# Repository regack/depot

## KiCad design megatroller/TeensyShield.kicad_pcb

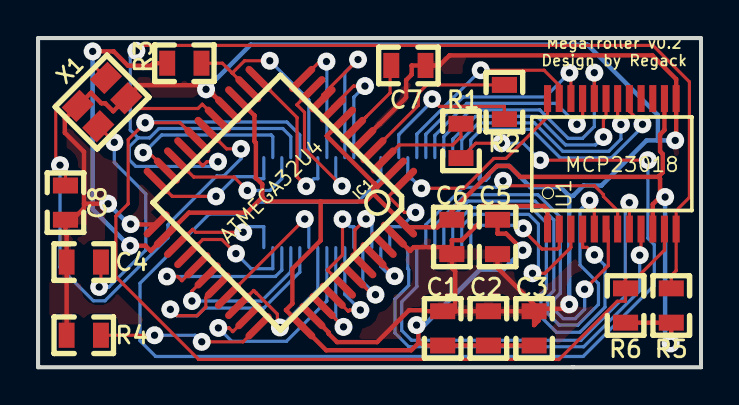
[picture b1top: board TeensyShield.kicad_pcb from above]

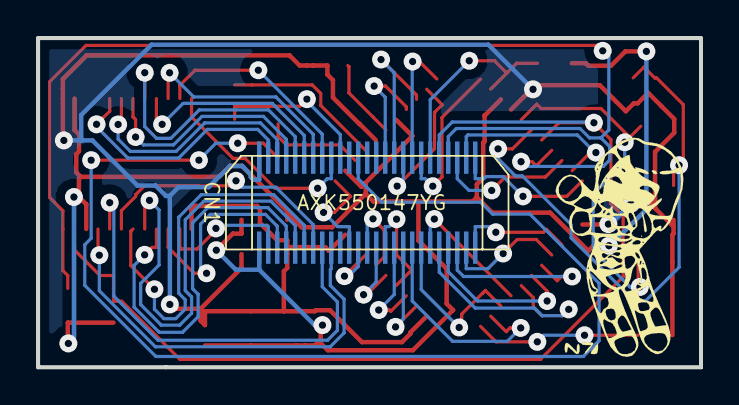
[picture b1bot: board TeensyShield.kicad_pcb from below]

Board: 2 copper layers, 36.8 x 18.3 mm, 19 parts (2 on the bottom side), 52 nets.

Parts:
C1, C7: 1u; SM0805
C2, C3, C5, C6: 100n; SM0805
C4, C8: 22p; SM0805
CN1: AXK550147YG; Panasonic_AXK550147YG_Socket
G1: LOGO; Silkscreen_Regack_100x150rev
IC1: ATMEGA32U4; TQFP44
R1, R2: 22Ω; SM0805
R3, R4: 10kΩ; SM0805
R5, R6: 2.2kΩ; SM0805
U1: MCP23018; SSOP24
X1: 7M-16.000MAAJ-T; ASX3F

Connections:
/GPA0: CN1.3, U1.17
/GPA1: CN1.5, U1.18
/GPA2: CN1.7, U1.19
/GPA3: CN1.9, U1.20
/GPA4: CN1.11, U1.21
/GPA5: CN1.13, U1.22
/GPA6: CN1.15, U1.23
/GPA7: CN1.17, U1.24
/GPB0: CN1.4, U1.2
/GPB1: CN1.6, U1.3
/GPB2: CN1.8, U1.4
/GPB3: CN1.10, U1.5
/GPB4: CN1.12, U1.6
/GPB5: CN1.14, U1.7
/GPB6: CN1.16, U1.8
/GPB7: CN1.18, U1.9
/PB0: CN1.29, IC1.8
/PB1: CN1.31, IC1.9
/PB2: CN1.33, IC1.10
/PB3: CN1.35, IC1.11
/PB4: CN1.44, IC1.28
/PB5: CN1.42, IC1.29
/PB6: CN1.40, IC1.30
/PB7: CN1.37, IC1.12
/PC6: CN1.38, IC1.31
/PC7: CN1.36, IC1.32
/PD0: CN1.41, IC1.18, R6.2, U1.11
/PD1: CN1.43, IC1.19, R5.2, U1.12
/PD2: CN1.45, IC1.20
/PD3: CN1.47, IC1.21
/PD4: CN1.50, IC1.25
/PD5: CN1.49, IC1.22
/PD6: CN1.48, IC1.26
/PD7: CN1.46, IC1.27
/PE6: CN1.22, IC1.1
/PF0: CN1.24, IC1.41
/PF1: CN1.26, IC1.40
/PF4: CN1.28, IC1.39
/PF5: CN1.30, IC1.38
/PF6: CN1.32, IC1.37
/PF7: CN1.34, IC1.36
/RST: CN1.39, IC1.13, R3.2
/USB_D+: CN1.19, R2.1
/USB_D-: CN1.23, R1.1
GND: C1.2, C2.2, C3.2, C4.2, C5.2, C6.2, C7.2, C8.2, CN1.1, IC1.5, IC1.15, IC1.23, IC1.35, IC1.43, R4.2, U1.1, U1.13, X1.2, X1.4
unnamed: C4.1, IC1.16, X1.1
unnamed: C7.1, IC1.6
unnamed: IC1.4, R2.2
unnamed: IC1.3, R1.2
unnamed: IC1.33, R4.1
unnamed: C8.1, IC1.17, X1.3
VCC: C1.1, C2.1, C3.1, C5.1, C6.1, CN1.2, IC1.2, IC1.7, IC1.14, IC1.24, IC1.34, IC1.44, R3.1, R5.1, R6.1, U1.10, U1.14

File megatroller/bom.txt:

ref             value           Item count      Mfr #                   footprint       datasheet
==========================================================================================================
C1, C7          1uF             1               VJ0805Y105JXQTW1BC      0805            https://www.mouser.com/Search/ProductDetail.aspx?R=VJ0805Y10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
C2,C3, C5, C6   0.1uF           2               VJ0805Y104JXXAC 0805                    https://www.mouser.com/Search/ProductDetail.aspx?R=VJ0805Y10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 
C4, C8          22pF            2               VJ0805A220GXXCW1BC      0805            https://www.mouser.com/Search/ProductDetail.aspx?R=VJ0805A22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 
CN1             AXK550147YG     1               AXK550147YG                             https://www.mouser.com/Search/ProductDetail.aspx?R=AXK550147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
IC1             ATMEGA32U4      1               ATMEGA32U4-AU-ND        TQFP44          https://www.mouser.com/Search/ProductDetail.aspx?R=ATMEGA32U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
R1,R2           22O             2               CRCW080522R0JNTABC      0805            http://www.tme.eu/pl/Document/e5152f6c2c4f933b61676f6de7ae79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
R3,R4           10kO            2               CRCW080510K0JNTABC      0805            http://www.tme.eu/pl/Document/e5152f6c2c4f933b61676f6de7ae79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
R5,R6           2.2kO           2               CRCW080522R0JNTABC      0805            http://www.tme.eu/pl/Document/e5152f6c2c4f933b61676f6de7ae79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
U1              MCP23018        1               MCP23018-E/SS           SSOP24          https://www.mouser.com/Search/ProductDetail.aspx?R=MCP23018-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
X1              7M-16.000MAAJ-T 1               7M-16.000MAAJ-T                         https://www.mouser.com/Search/ProductDetail.aspx?R=7M-16.000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

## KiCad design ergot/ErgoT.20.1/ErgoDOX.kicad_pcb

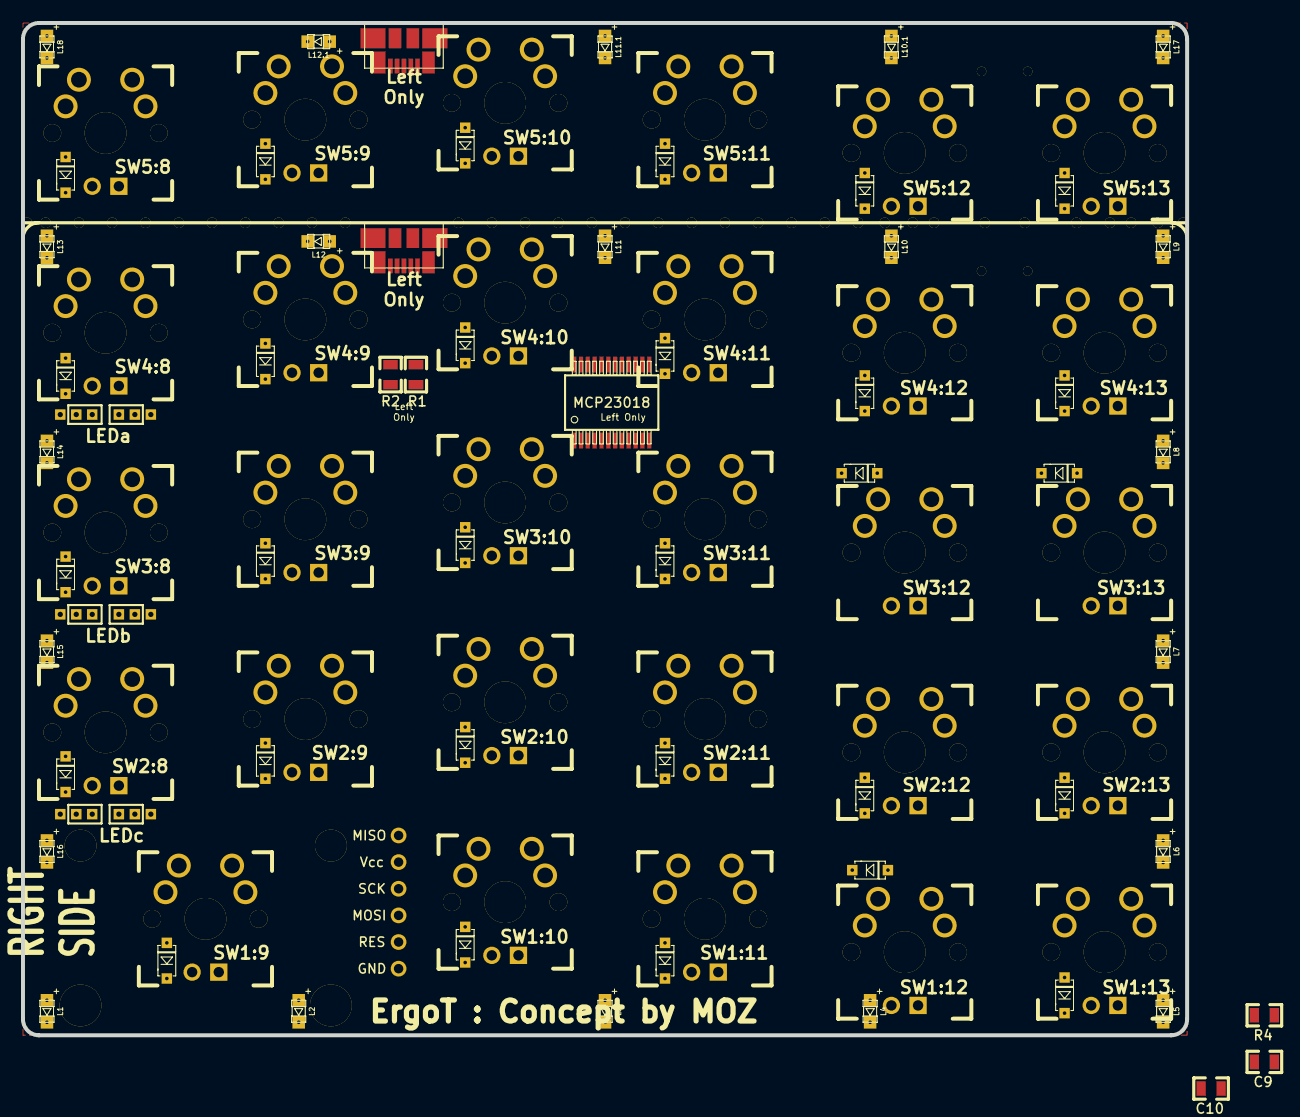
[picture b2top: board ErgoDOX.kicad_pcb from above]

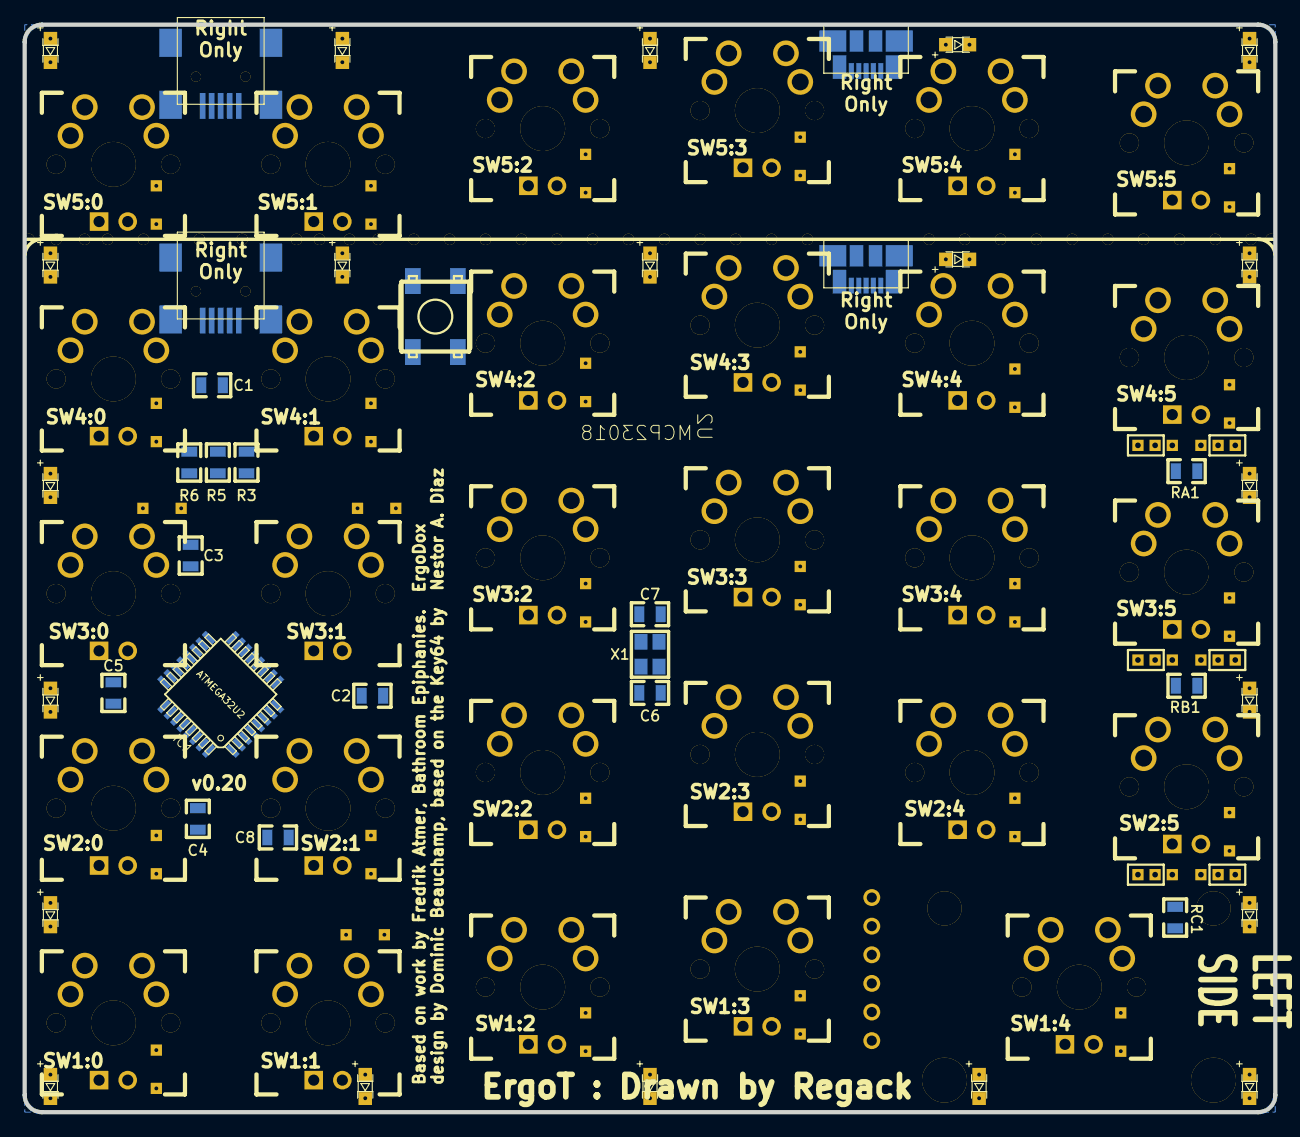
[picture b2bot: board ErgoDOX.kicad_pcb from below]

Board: 2 copper layers, 111.0 x 96.5 mm, 184 parts (21 on the bottom side), 81 nets, no tracks yet.

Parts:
C1, C8: 1u; SM0805
C2, C3, C4, C5: 100n; SM0805
C6, C7: 22p; SM0805
C9: 10μF; SM0805
C10: 0.1μF; SM0805
D1:9: D1:4; SOD-123_2Side
D1:10: D1:3; SOD-123_2Side
D1:11: D1:2; SOD-123_2Side
D1:12: D1:1; SOD-123_2Side
D1:13: D1:0; SOD-123_2Side
D2:8: D2:5; SOD-123_2Side
D2:9: D2:4; SOD-123_2Side
D2:10: D2:3; SOD-123_2Side
D2:11: D2:2; SOD-123_2Side
D2:12: D2:1; SOD-123_2Side
D2:13: D2:0; SOD-123_2Side
D3:8: D3:5; SOD-123_2Side
D3:9: D3:4; SOD-123_2Side
D3:10: D3:3; SOD-123_2Side
D3:11: D3:2; SOD-123_2Side
D3:12: D3:1; SOD-123_2Side
D3:13: D3:0; SOD-123_2Side
D4:8: D4:5; SOD-123_2Side
D4:9: D4:4; SOD-123_2Side
D4:10: D4:3; SOD-123_2Side
D4:11: D4:2; SOD-123_2Side
D4:12: D4:1; SOD-123_2Side
D4:13: D4:0; SOD-123_2Side
D5:8: D5:5; SOD-123_2Side
D5:9: D5:4; SOD-123_2Side
D5:10: D5:3; SOD-123_2Side
D5:11: D5:2; SOD-123_2Side
D5:12: D5:1; SOD-123_2Side
D5:13: D5:0; SOD-123_2Side
IC1: ATMEGA32U2; adafruit-TQFP32-08
J1, J1.1: USB; USB_MINI-B_OST_M26FTR
J2.1, J2.1.1: LEFT(TOP); USB_MICRO-B_MOLEX_47346-0001
J2.2, J2.2.1: RIGHT(BOTTOM); USB_MICRO-B_MOLEX_47346-0001
JP1, JP2, JP3, JP4, JP5, JP6: JUMPER3; 40milX3
L1, L2, L3, L4, L5, L6, L7, L8, L9, L10, L10.1, L11, L11.1, L12, L12.1, L13, L14, L15, L16, L17, L18: LED; LED0805_(1-2)_2Side
L1:0, L1:1, L1:2, L1:3, L1:4, L2:0, L2:1, L2:2, L2:3, L2:4, L2:5, L3:0, L3:1, L3:2, L3:3, L3:4, L3:5, L4:0, L4:1, L4:2, L4:3, L4:4, L4:5, L5:0, L5:1, L5:2, L5:3, L5:4, L5:5: LED; MX_LED
M1, M2, M3, M4, M5, M6, M7, M8, M9, M10, M11, M12, M13, M14, M15, M16, M17, M18, M19, M20, M21, M22, M23, M24, M25, M26, M27, M28, M29, M30, M31, M32, M33, M34: DRILL; Pad_Drl
P1: MISO; Pad
P4: Vcc; Pad
P5: SCK; Pad
P6: MOSI; Pad
P7: RES; Pad
P8: GND; Pad
R1, R2: 2.2kΩ; SM0805
R3: 10k; SM0805
R4: 22.6k; SM0805
R5, R6: 22; SM0805
RA1: LEDa; SM0805
RB1: LEDb; SM0805
RC1: LEDc; SM0805
S0: DTSM-6; ADTSJW65RV
S2: STAB200; STAB_PCB940
SW1:9: SW1:4; MX_FLIP
SW1:10: SW1:3; MX_FLIP
SW1:11: SW1:2; MX_FLIP
SW1:12: SW1:1; MX_FLIP
SW1:13: SW1:0; MX_FLIP
SW2:8: SW2:5; MX_FLIP
SW2:9: SW2:4; MX_FLIP
SW2:10: SW2:3; MX_FLIP
SW2:11: SW2:2; MX_FLIP
SW2:12: SW2:1; MX_FLIP
SW2:13: SW2:0; MX_FLIP
SW3:8: SW3:5; MX_FLIP
SW3:9: SW3:4; MX_FLIP
SW3:10: SW3:3; MX_FLIP
SW3:11: SW3:2; MX_FLIP
SW3:12: SW3:1; MX_FLIP
SW3:13: SW3:0; MX_FLIP
SW4:8: SW4:5; MX_FLIP
SW4:9: SW4:4; MX_FLIP
SW4:10: SW4:3; MX_FLIP
SW4:11: SW4:2; MX_FLIP
SW4:12: SW4:1; MX_FLIP
SW4:13: SW4:0; MX_FLIP
SW5:8: SW5:5; MX_FLIP
SW5:9: SW5:4; MX_FLIP
SW5:10: SW5:3; MX_FLIP
SW5:11: SW5:2; MX_FLIP
SW5:12: SW5:1; MX_FLIP
SW5:13: SW5:0; MX_FLIP
U2: MCP23018; adafruit-SSOP24
X1: ASX3F

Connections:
/COL0: D1:13.2, D2:13.2, D3:13.2, D4:13.2, D5:13.2, IC1.11, U2.17
/COL1: D1:12.2, D2:12.2, D3:12.2, D4:12.2, D5:12.2, IC1.10, U2.18
/COL4: D1:9.2, D2:9.2, D3:9.2, D4:9.2, D5:9.2, IC1.7, U2.21
/COL5: D2:8.2, D3:8.2, D4:8.2, D5:8.2, IC1.6, U2.22
/COL10: D1:10.2, D2:10.2, D3:10.2, D4:10.2, D5:10.2, IC1.8, U2.20
/COL11: D1:11.2, D2:11.2, D3:11.2, D4:11.2, D5:11.2, IC1.9, U2.19
/DIG0: L5:0.2, L5:1.2, L5:2.2, L5:3.2, L5:4.2, L5:5.2
/DIG1: JP6.3, L4:0.2, L4:1.2, L4:2.2, L4:3.2, L4:4.2
/DIG2: JP4.3, L3:0.2, L3:1.2, L3:2.2, L3:3.2, L3:4.2
/DIG3: JP2.3, L2:0.2, L2:1.2, L2:2.2, L2:3.2, L2:4.2
/DIG4: L1:0.2, L1:1.2, L1:2.2, L1:3.2, L1:4.2
/DIG5: L1.2, L2.2, L3.2, L4.2, L5.2, L6.2
/DIG6: L7.2, L8.2, L9.2, L10.2, L11.2, L12.2
/DIG7: L13.2, L14.2, L15.2, L16.2, L17.2, L18.2
/LED_2:5A: JP1.3, JP3.3, JP5.3, L1.1, L5:5.1, L7.1, L13.1
/LED_A: IC1.19, RA1.1
/LED_B: IC1.20, RB1.1
/LED_C: IC1.21, RC1.1
/MISO: IC1.17, P1.1
/MOSI: IC1.16, P6.1
/ROW1: IC1.5, SW1:9.1, SW1:10.1, SW1:11.1, SW1:12.1, SW1:13.1, U2.6
/ROW2: IC1.26, SW2:8.1, SW2:9.1, SW2:10.1, SW2:11.1, SW2:12.1, SW2:13.1, U2.5
/ROW3: IC1.25, SW3:8.1, SW3:9.1, SW3:10.1, SW3:11.1, SW3:12.1, SW3:13.1, U2.4
/ROW4: IC1.23, SW4:8.1, SW4:9.1, SW4:10.1, SW4:11.1, SW4:12.1, SW4:13.1, U2.3
/ROW5: IC1.22, SW5:8.1, SW5:9.1, SW5:10.1, SW5:11.1, SW5:12.1, SW5:13.1, U2.2
/SCK: IC1.15, P5.1
/SCL: IC1.13, J2.1.3, J2.1.1.3, J2.2.3, J2.2.1.3, R2.2, U2.11
/SDA: IC1.12, J2.1.2, J2.1.1.2, J2.2.2, J2.2.1.2, R1.2, U2.12
/SEGB: L1:4.1, L2.1, L2:4.1, L3:4.1, L4:4.1, L5:4.1, L8.1, L14.1
/SEGC: L1:3.1, L2:3.1, L3.1, L3:3.1, L4:3.1, L5:3.1, L9.1, L15.1
/SEGD: L1:2.1, L2:2.1, L3:2.1, L4.1, L4:2.1, L5:2.1, L10.1, L16.1
/SEGE: L1:1.1, L2:1.1, L3:1.1, L4:1.1, L5.1, L5:1.1, L11.1, L17.1
/SEGF: L1:0.1, L2:0.1, L3:0.1, L4:0.1, L5:0.1, L6.1, L12.1, L18.1
/USBD+: IC1.29, R6.1
/USBD-: IC1.30, R5.1
/XTAL1: C7.1, IC1.1, X1.3
/XTAL2: C6.1, IC1.2, X1.1
/~RES~: IC1.24, P7.1, R3.2, S0.3
GND: C1.2, C2.2, C3.2, C4.2, C5.2, C6.2, C7.2, C8.2, C9.2, C10.2, IC1.3, IC1.28, J1.5, J1.1.5, J2.1.5, J2.1.1.5, J2.2.5, J2.2.1.5, JP2.1, JP4.1, JP6.1, P8.1, S0.1, U2.1, U2.13, X1.2, X1.4
unnamed: D5:9.1, SW5:9.2
unnamed: D1:12.1, SW1:12.2
unnamed: D1:11.1, SW1:11.2
unnamed: D1:10.1, SW1:10.2
unnamed: D1:9.1, SW1:9.2
unnamed: D3:13.1, SW3:13.2
unnamed: J1.3, J1.1.3, R6.2
unnamed: J1.2, J1.1.2, R5.2
unnamed: D1:13.1, SW1:13.2
unnamed: D3:12.1, SW3:12.2
unnamed: D4:12.1, SW4:12.2
unnamed: D4:11.1, SW4:11.2
unnamed: D4:10.1, SW4:10.2
unnamed: D4:9.1, SW4:9.2
unnamed: D4:8.1, SW4:8.2
unnamed: D4:13.1, SW4:13.2
unnamed: D3:11.1, SW3:11.2
unnamed: D3:10.1, SW3:10.2
unnamed: D3:9.1, SW3:9.2
unnamed: D3:8.1, SW3:8.2
unnamed: D2:12.1, SW2:12.2
unnamed: D2:13.1, SW2:13.2
unnamed: D2:11.1, SW2:11.2
unnamed: D2:10.1, SW2:10.2
unnamed: D2:9.1, SW2:9.2
unnamed: D2:8.1, SW2:8.2
unnamed: JP6.2, L4:5.2
unnamed: JP5.2, L4:5.1
unnamed: JP5.1, RA1.2
unnamed: JP4.2, L3:5.2
unnamed: JP3.2, L3:5.1
unnamed: JP3.1, RB1.2
unnamed: JP2.2, L2:5.2
unnamed: JP1.2, L2:5.1
unnamed: JP1.1, RC1.2
unnamed: C8.1, IC1.27
unnamed: D5:10.1, SW5:10.2
unnamed: D5:13.1, SW5:13.2
unnamed: D5:12.1, SW5:12.2
unnamed: D5:11.1, SW5:11.2
unnamed: D5:8.1, SW5:8.2
VCC: C1.1, C2.1, C3.1, C4.1, C5.1, C9.1, C10.1, IC1.4, IC1.18, IC1.31, IC1.32, J1.1, J1.1.1, J2.1.1, J2.1.1.1, J2.2.1, J2.2.1.1, P4.1, R1.1, R2.1, R3.1, R4.1, U2.10, U2.14

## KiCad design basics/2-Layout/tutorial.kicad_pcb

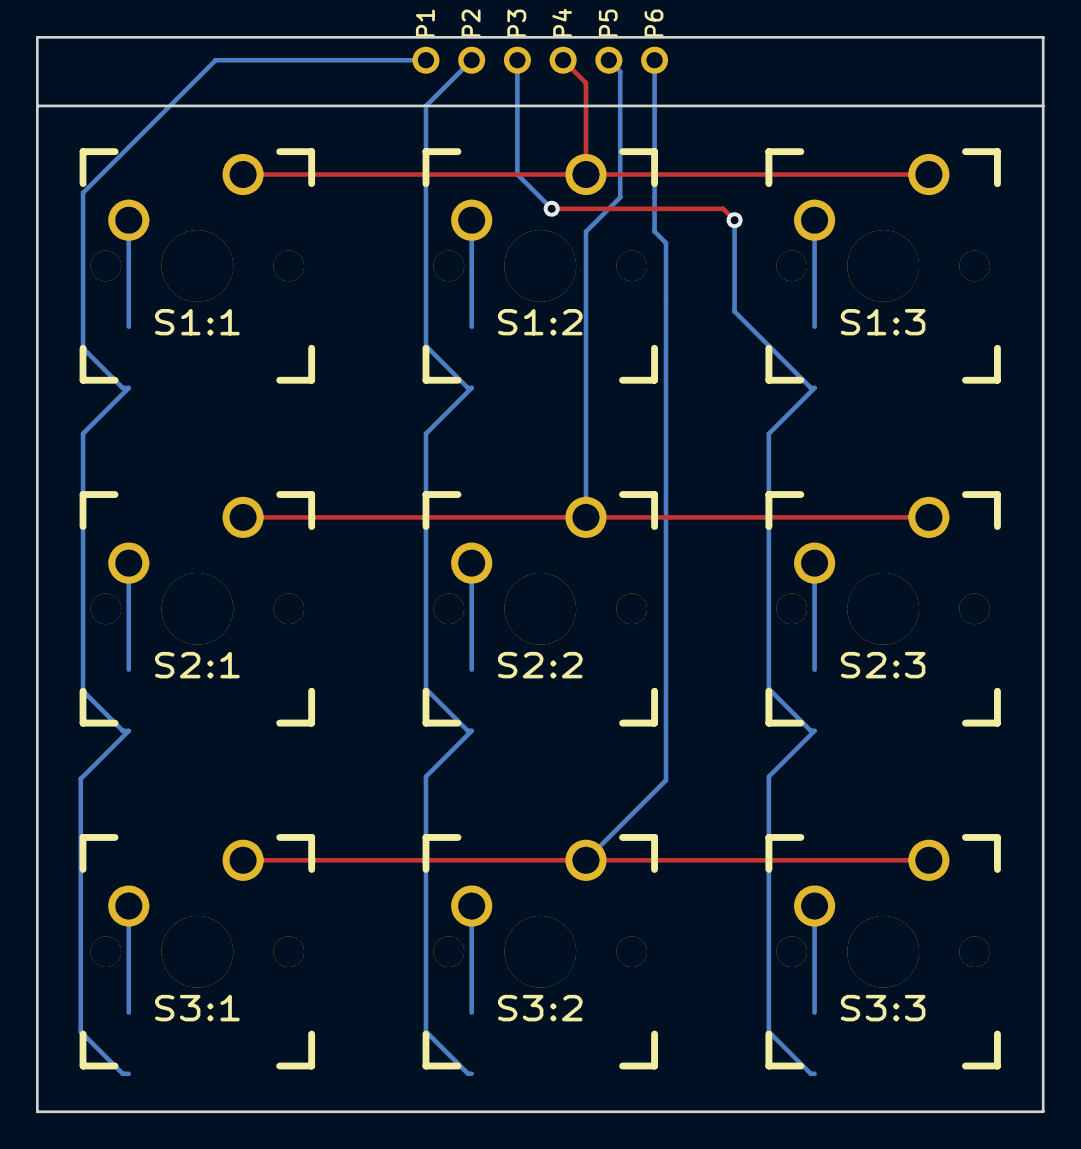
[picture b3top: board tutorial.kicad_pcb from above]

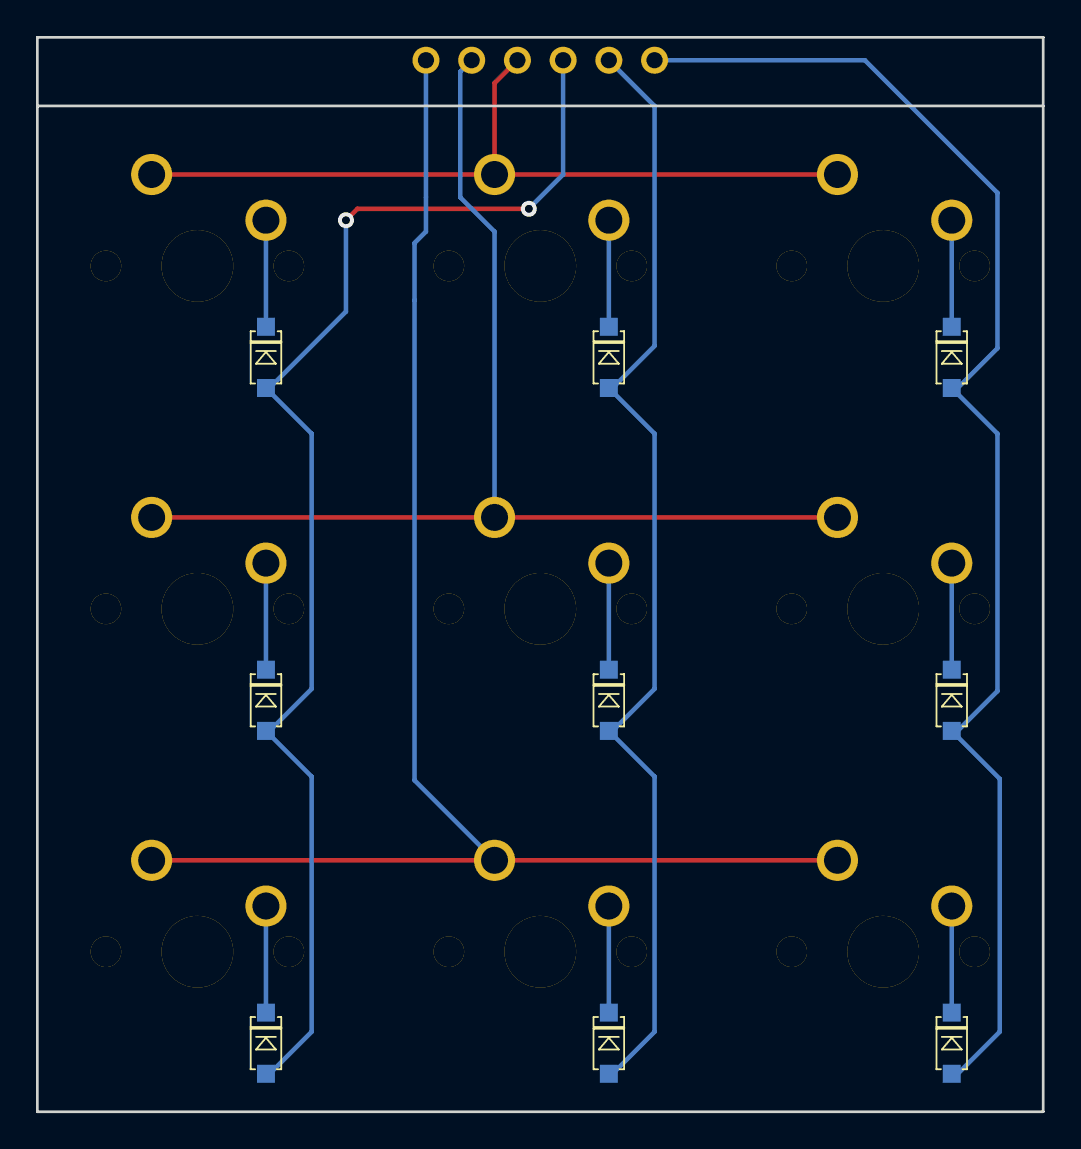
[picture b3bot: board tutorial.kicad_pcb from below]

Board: 2 copper layers, 55.9 x 59.7 mm, 24 parts (9 on the bottom side), 15 nets.

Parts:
D1:1, D1:2, D1:3, D2:1, D2:2, D2:3, D3:1, D3:2, D3:3: DIODE; SOD-123(A-C)
P1: COL1; Pad
P2: COL2; Pad
P3: COL3; Pad
P4: ROW1; Pad
P5: ROW2; Pad
P6: ROW3; Pad
S1:1, S1:2, S1:3, S2:1, S2:2, S2:3, S3:1, S3:2, S3:3: MX1A; CHERRY_PCB_100H_Plated

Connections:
unnamed: D2:3.C, S2:3.2
unnamed: D1:3.A, D2:3.A, D3:3.A, P3.1
unnamed: D3:3.C, S3:3.2
unnamed: D1:3.C, S1:3.2
unnamed: D1:1.A, D2:1.A, D3:1.A, P1.1
unnamed: D1:2.A, D2:2.A, D3:2.A, P2.1
unnamed: D3:1.C, S3:1.2
unnamed: D2:1.C, S2:1.2
unnamed: D1:1.C, S1:1.2
unnamed: D1:2.C, S1:2.2
unnamed: D3:2.C, S3:2.2
unnamed: D2:2.C, S2:2.2
unnamed: P4.1, S1:1.1, S1:2.1, S1:3.1
unnamed: P6.1, S3:1.1, S3:2.1, S3:3.1
unnamed: P5.1, S2:1.1, S2:2.1, S2:3.1

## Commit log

2014-01-18 tutorial
2014-01-20 basic libs/mods
2014-02-05 ergot
2014-02-19 megatroller v2
